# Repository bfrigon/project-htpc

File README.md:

HTPC
====

Project page at http://www.bfrigon.com/posts/projects/htpc/

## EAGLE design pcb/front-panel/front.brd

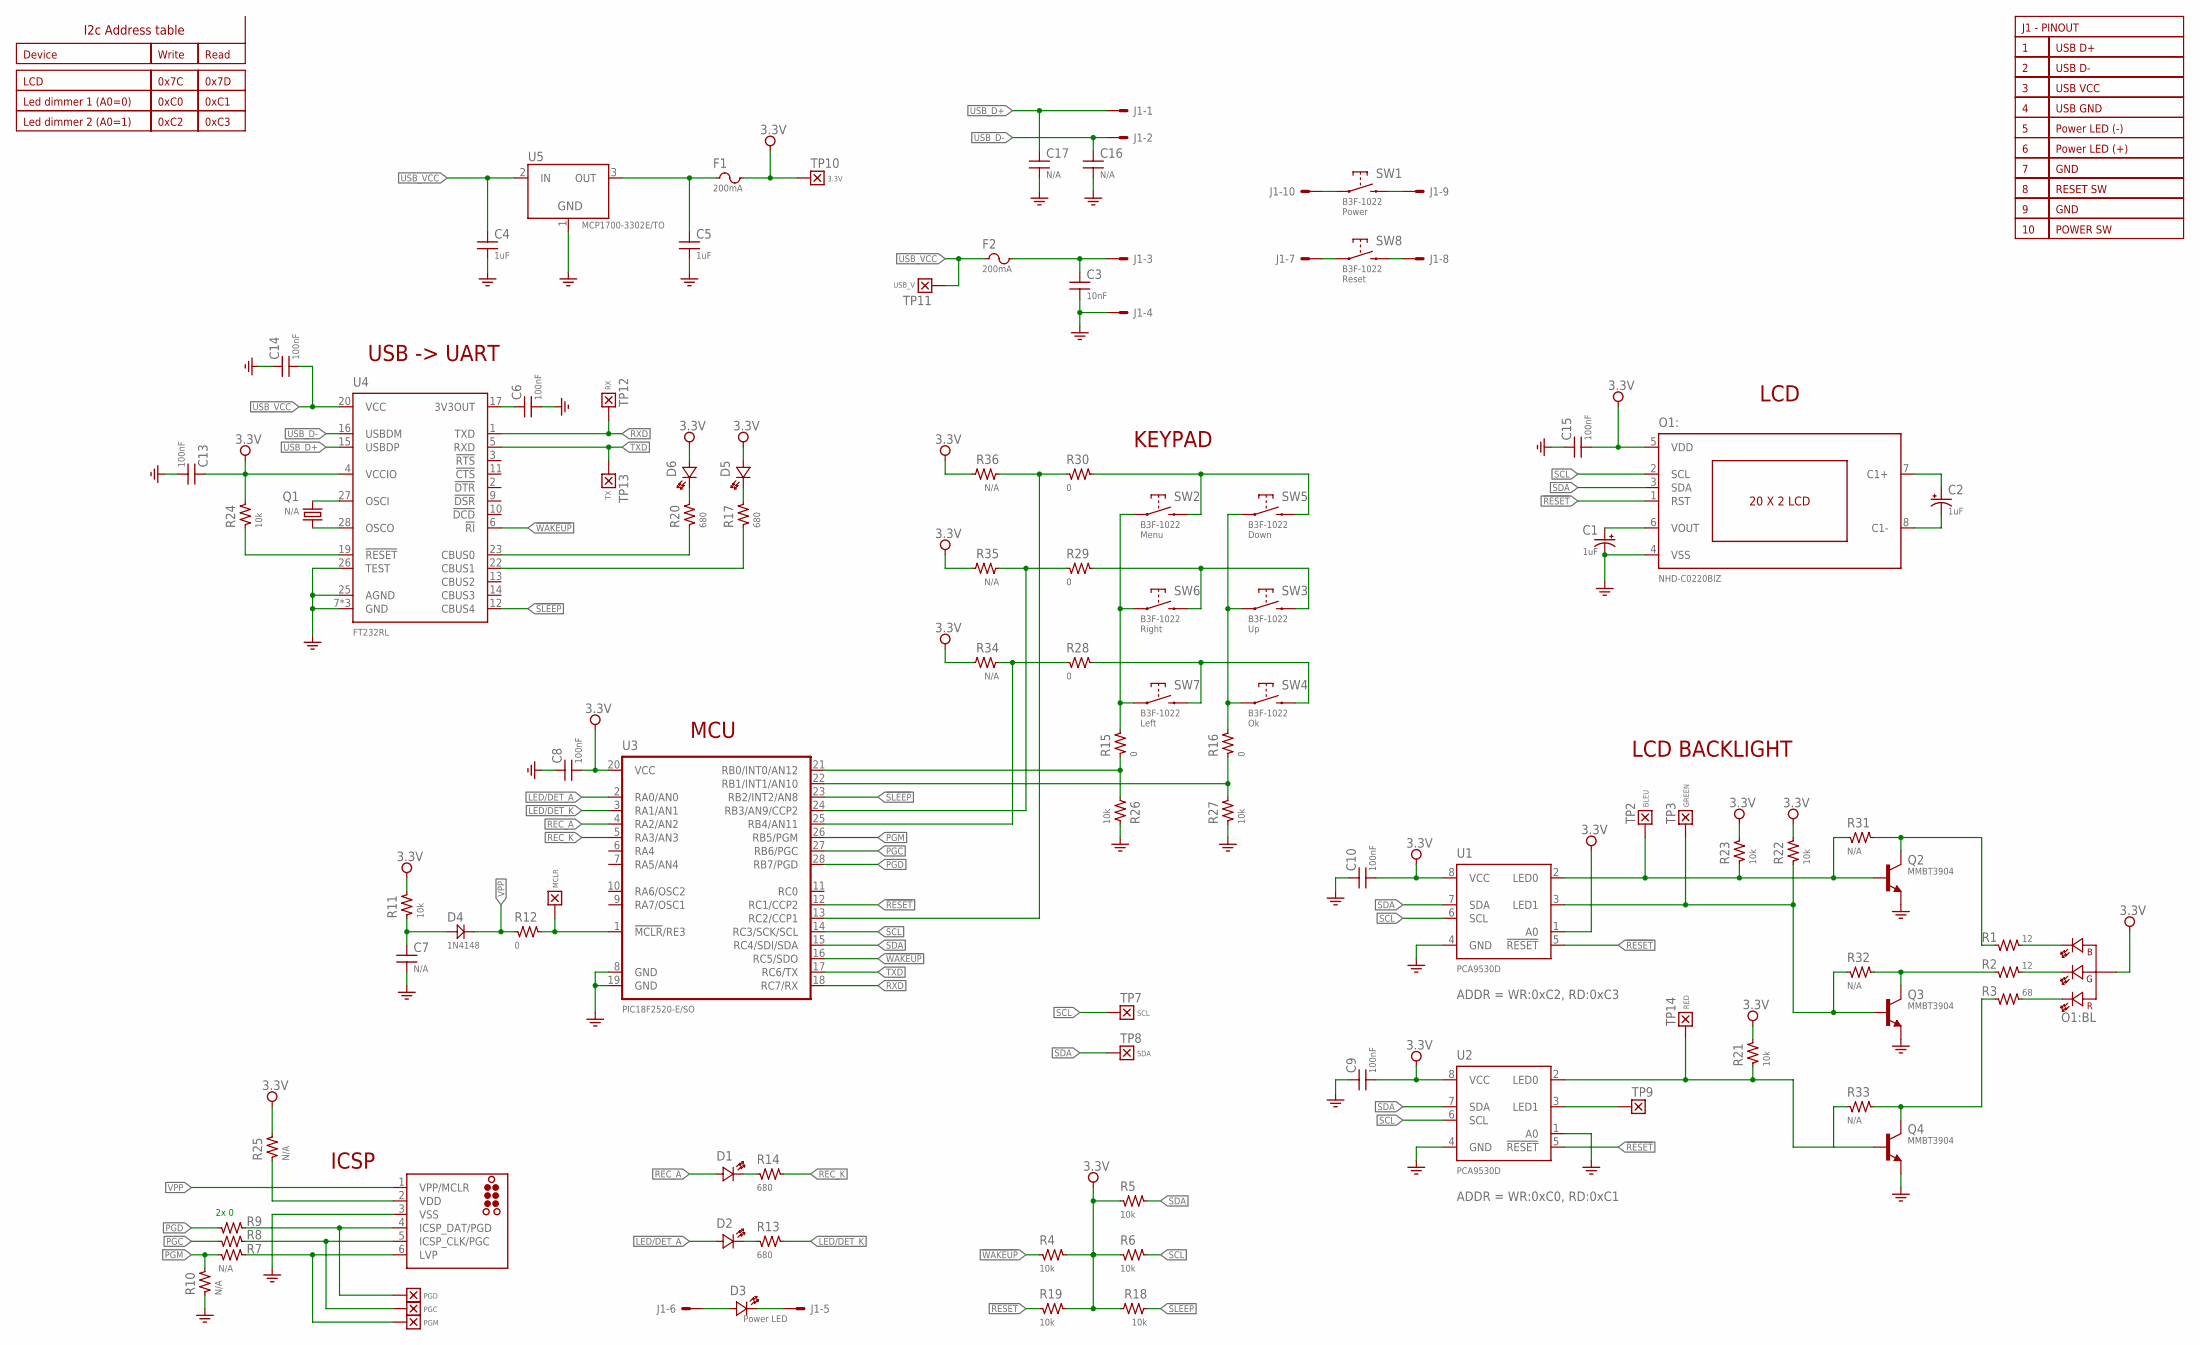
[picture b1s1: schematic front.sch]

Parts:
C1, C2: 1uF; CAP_S0805
C3: 10nF; SMD_0805
C4, C5: 1uF; SMD_0805
C6, C8, C9, C10, C13, C14, C15: 100nF; SMD_0603
C7, C16, C17: N/A; SMD_0603
D1, D2, D3: {ATTR:COLOR}; LED_2X5
D4: 1N4148; DIODE_0603
D5, D6: LED-0805; CHIPLED_0805
F1, F2: 200mA; SMD_1206
J1: DL-100-HEADER-10-V; 534206-5
J10: TC2030-MCP
O1: NHD-C0220BIZ; NHD-CO220BIZ
Q1: N/A; MM20SS
Q2, Q3, Q4: MMBT3904; SOT23
R1, R2: 12; SMD_1206
R3: 68; SMD_1206
R4, R5, R6, R18, R19, R21, R22, R23: 10k; SMD_0805
R7, R10, R25, R34, R35, R36: N/A; SMD_0603
R8, R9, R12, R28: 0; SMD_0603
R11, R24, R26, R27: 10k; SMD_0603
R13, R14, R17, R20: 680; SMD_0805
R15, R16, R29, R30: 0; SMD_0805
R31, R32, R33: N/A; SMD_1206
SW1, SW2, SW3, SW4, SW5, SW6, SW7, SW8: B3F-1022; B3F-10XX
TP1: MCLR; TP_050
TP2: BLEU; TP_050
TP3: GREEN; TP_050
TP4: PGD; TP_050
TP5: PGC; TP_050
TP6: PGM; TP_050
TP7: SCL; TP_050
TP8: SDA; TP_050
TP9: TEST_POINT-050; TP_050
TP10: 3.3V; TP_050
TP11: USB_V; TP_050
TP12: RX; TP_050
TP13: TX; TP_050
TP14: RED; TP_050
U1, U2: PCA9530D; SOIC8
U3: PIC18F2520-E/SO; SOIC28
U4: FT232RL; SSOP28
U5: MCP1700-3302E/TO; TO92

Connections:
3.3V: C8.2, C9.2, C10.2, C13.1, C15.2, D5.A, D6.A, F1.2, O1.5 (VDD), O1.A, R4.2, R5.1, R6.1, R11.2, R18.2, R19.2, R21.2, R22.2, R23.2, R24.2, R25.2, R34.2, R35.2, R36.2, TP10.1, U1.1 (A0), U1.8 (VCC), U2.8 (VCC), U3.20 (VCC), U4.4 (VCCIO)
!RESET: O1.1 (RST), R19.1, U1.5 (!RESET), U2.5 (!RESET), U3.12 (RC1/CCP2)
!SLEEP: R18.1, U3.23 (RB2/INT2/AN8), U4.12 (CBUS4)
!WAKEUP: R4.1, U3.16 (RC5/SDO), U4.6 (!RI)
GND: C1.-, C3.2, C4.2, C5.2, C6.2, C7.2, C8.1, C9.1, C10.1, C13.2, C14.1, C15.1, C16.2, C17.2, J1.4, J10.3 (VSS), O1.4 (VSS), Q2.2 (E), Q3.2 (E), Q4.2 (E), R10.1, R26.1, R27.1, U1.4 (GND), U2.1 (A0), U2.4 (GND), U3.8 (GND), U3.19 (GND), U4.7 (GND), U4.18 (GND), U4.21 (GND), U4.25 (AGND), U4.26 (TEST), U5.1 (GND)
LED/DET_A: D2.A, U3.2 (RA0/AN0)
LED/DET_K: R13.2, U3.3 (RA1/AN1)
unnamed: O1.BK, R1.2
unnamed: O1.GK, R2.2
unnamed: O1.RK, R3.2
unnamed: Q2.1 (B), R23.1, R31.1, TP2.1, U1.2 (LED0)
unnamed: Q3.1 (B), R22.1, R32.1, TP3.1, U1.3 (LED1)
unnamed: Q2.3 (C), R1.1, R31.2
unnamed: J1.10, SW1.3 (1), SW1.4 (1)
unnamed: J1.9, SW1.1 (2), SW1.2
unnamed: J1.8, SW8.1 (2), SW8.2
unnamed: J1.7, SW8.3 (1), SW8.4 (1)
unnamed: D3.A, J1.6
unnamed: D3.K, J1.5
unnamed: C6.1, U4.17 (3V3OUT)
unnamed: J10.6 (LVP), R7.2, TP6.1
unnamed: J10.5 (ICSP_CLK/PGC), R8.2, TP5.1
unnamed: J10.4 (ICSP_DAT/PGD), R9.2, TP4.1
unnamed: R15.1, R26.2, U3.21 (RB0/INT0/AN12)
unnamed: R16.1, R27.2, U3.22 (RB1/INT1/AN10)
unnamed: R30.1, R36.1, U3.13 (RC2/CCP1)
unnamed: R29.1, R35.1, U3.24 (RB3/AN9/CCP2)
unnamed: R28.1, R34.1, U3.25 (RB4/AN11)
unnamed: R12.2, TP1.1, U3.1 (!MCLR!/RE3)
unnamed: D2.K, R13.1
unnamed: R15.2, SW2.3 (1), SW2.4 (1), SW6.3 (1), SW6.4 (1), SW7.3 (1), SW7.4 (1)
unnamed: D1.K, R14.1
unnamed: R16.2, SW3.3 (1), SW3.4 (1), SW4.3 (1), SW4.4 (1), SW5.3 (1), SW5.4 (1)
unnamed: R17.1, U4.22 (CBUS1)
unnamed: R20.1, U4.23 (CBUS0)
unnamed: D6.K, R20.2
unnamed: D5.K, R17.2
unnamed: Q3.3 (C), R2.1, R32.2
unnamed: Q4.3 (C), R3.1, R33.2
unnamed: C5.1, F1.1, U5.3 (OUT)
unnamed: Q4.1 (B), R21.1, R33.1, TP14.1, U2.2 (LED0)
unnamed: C3.1, F2.2, J1.3
unnamed: Q1.1, U4.27 (OSCI)
unnamed: Q1.4 (2), U4.28 (OSCO)
unnamed: C2.+, O1.7 (C1+)
unnamed: C2.-, O1.8 (C1-)
unnamed: C1.+, O1.6 (VOUT)
unnamed: TP9.1, U2.3 (LED1)
unnamed: R24.1, U4.19 (!RESET)
unnamed: J10.2 (VDD), R25.1
unnamed: C7.1, D4.A, R11.1
unnamed: R30.2, SW2.1 (2), SW2.2, SW5.1 (2), SW5.2
unnamed: R29.2, SW3.1 (2), SW3.2, SW6.1 (2), SW6.2
unnamed: R28.2, SW4.1 (2), SW4.2, SW7.1 (2), SW7.2
PGC: R8.1, U3.27 (RB6/PGC)
PGD: R9.1, U3.28 (RB7/PGD)
PGM: R7.1, R10.2, U3.26 (RB5/PGM)
REC_A: D1.A, U3.4 (RA2/AN2)
REC_K: R14.2, U3.5 (RA3/AN3)
RXD: TP12.1, U3.18 (RC7/RX), U4.1 (TXD)
SCL: O1.2 (SCL), R6.2, TP7.1, U1.6 (SCL), U2.6 (SCL), U3.14 (RC3/SCK/SCL)
SDA: O1.3 (SDA), R5.2, TP8.1, U1.7 (SDA), U2.7 (SDA), U3.15 (RC4/SDI/SDA)
TXD: TP13.1, U3.17 (RC6/TX), U4.5 (RXD)
USB_D+: C17.1, J1.1, U4.15 (USBDP)
USB_D-: C16.1, J1.2, U4.16 (USBDM)
USB_VCC: C4.1, C14.2, F2.1, TP11.1, U4.20 (VCC), U5.2 (IN)
VPP: D4.K, J10.1 (VPP/MCLR), R12.1

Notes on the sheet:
I2c Address table
LCD BACKLIGHT
USB -> UART
ICSP
LCD
MCU
2x 0
KEYPAD

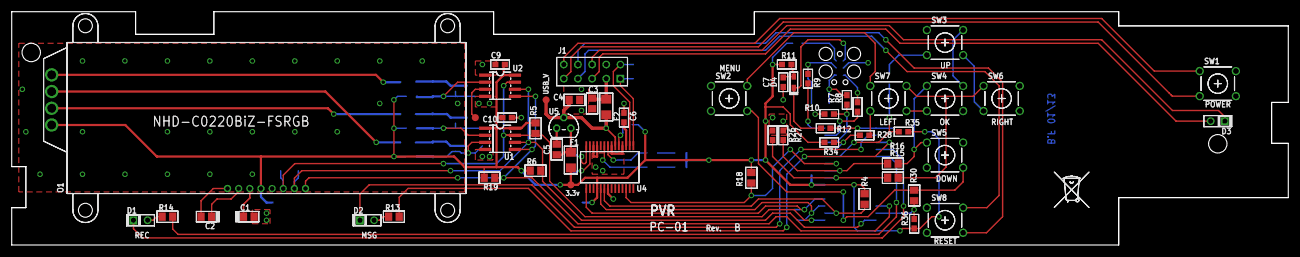
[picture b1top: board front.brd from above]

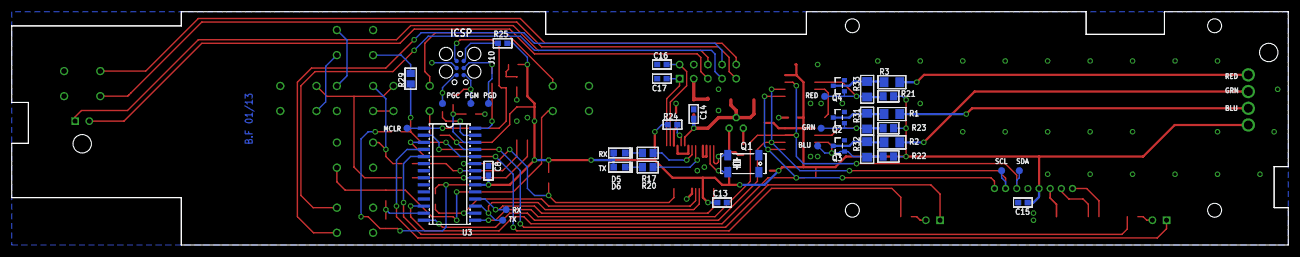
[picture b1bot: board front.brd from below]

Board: 2 copper layers, 229.1 x 41.9 mm, 97 parts (41 on the bottom side), 67 nets.

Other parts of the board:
U$1: INFO
U$2: TRASH_SMALL
U$3: INFO_AUTHOR
U$4: INFO_DATE

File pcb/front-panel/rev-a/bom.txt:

Qty. Part ID                                Description                                      Mfg. SKU              Manufacturer                Package      Value
1    X1                                     10 Pos - Dual Row - 2.54mm Receptacle - Vertical SIP110-PPPC-D05-ST-BK Sullins Connector Solutions 534206-5     -    
8    SW1, SW2, SW3, SW4, SW5, SW6, SW7, SW8 Tactile switch - 6x6mm - 5mm Pitch - 150g        B3F-1022              Omron Electronics           B3F-10XX     -    
1    O1                                     Alphanumeric LCD module 20x2 - RGB Backlight     NHD-C0220BIZ          Newheaven Display           NHD-CO220BIZ -    
2    U1, U2                                 8-bit I2C-bus LED dimmer                         PCA9530D              NXP Semiconductors          SOIC8        -    
1    U3                                     Microcontroller 32k PROG / 1536 RAM / 256 EEPROM PIC18F2520-E/SO       -                           SOIC28       -    
3    T1, T2, T3                             PNP Transistor                                   MMBT3906              -                           SOT23-BEC    -    
1    U4                                     USB to serial UART interface                     FT232RL               -                           SSOP28       -    
1    U5                                     Low-dropout (LDO) Voltage Regulator - 3.3v       MCP1700-3302E/TO      Microchip                   TO92         -    
4    R7, R8, R9, R12                        Resistor - SMT 0603 - 0                          -                     -                           SMT 0603     0    
3    L1, R15, R16                           Resistor - SMT 0805 - 0                          -                     -                           SMT 0805     0    
2    C1, C2                                 Electrolytic capacitor - SMT 0805 - 1uF          -                     -                           CAP_S0805    1uF  
2    C4, C5                                 Capacitor - SMT 0805 - 1uF                       -                     -                           SMT 0805     1uF  
2    R1, R2                                 Resistor - SMT 1206 - 6.8                        -                     -                           SMT 1206     6.8  
3    R10, R11, R17                          Resistor - SMT 0603 - 10k                        -                     -                           SMT 0603     10k  
5    R4, R5, R6, R18, R19                   Resistor - SMT 0805 - 10k                        -                     -                           SMT 0805     10k  
1    C3                                     Capacitor - SMT 0805 - 10nF                      -                     -                           SMT 0805     10nF 
1    R3                                     Resistor - SMT 1206 - 33                         -                     -                           SMT 1206     33   
2    C16, C17                               Capacitor - SMT 0603 - 47nF                      -                     -                           SMT 0603     47nF 
7    C6, C8, C9, C10, C13, C14, C15         Capacitor - SMT 0603 - 100nF                     -                     -                           SMT 0603     100nF
2    F1, F2                                 Fuse - SMT 1206 - 250mA                          -                     -                           SMD_1206     250mA
3    R13, R14, R20                          Resistor - SMT 0805 - 680                        -                     -                           SMT 0805     680  
2    D2, D3                                 Led 2x5mm - Green                                -                     -                           2x5mm        Green
1    D6                                     Led Chip 0805 - Green                            -                     -                           SMT 0805     Green
1    D1                                     Led 2x5mm - Red                                  -                     -                           2x5mm        Red

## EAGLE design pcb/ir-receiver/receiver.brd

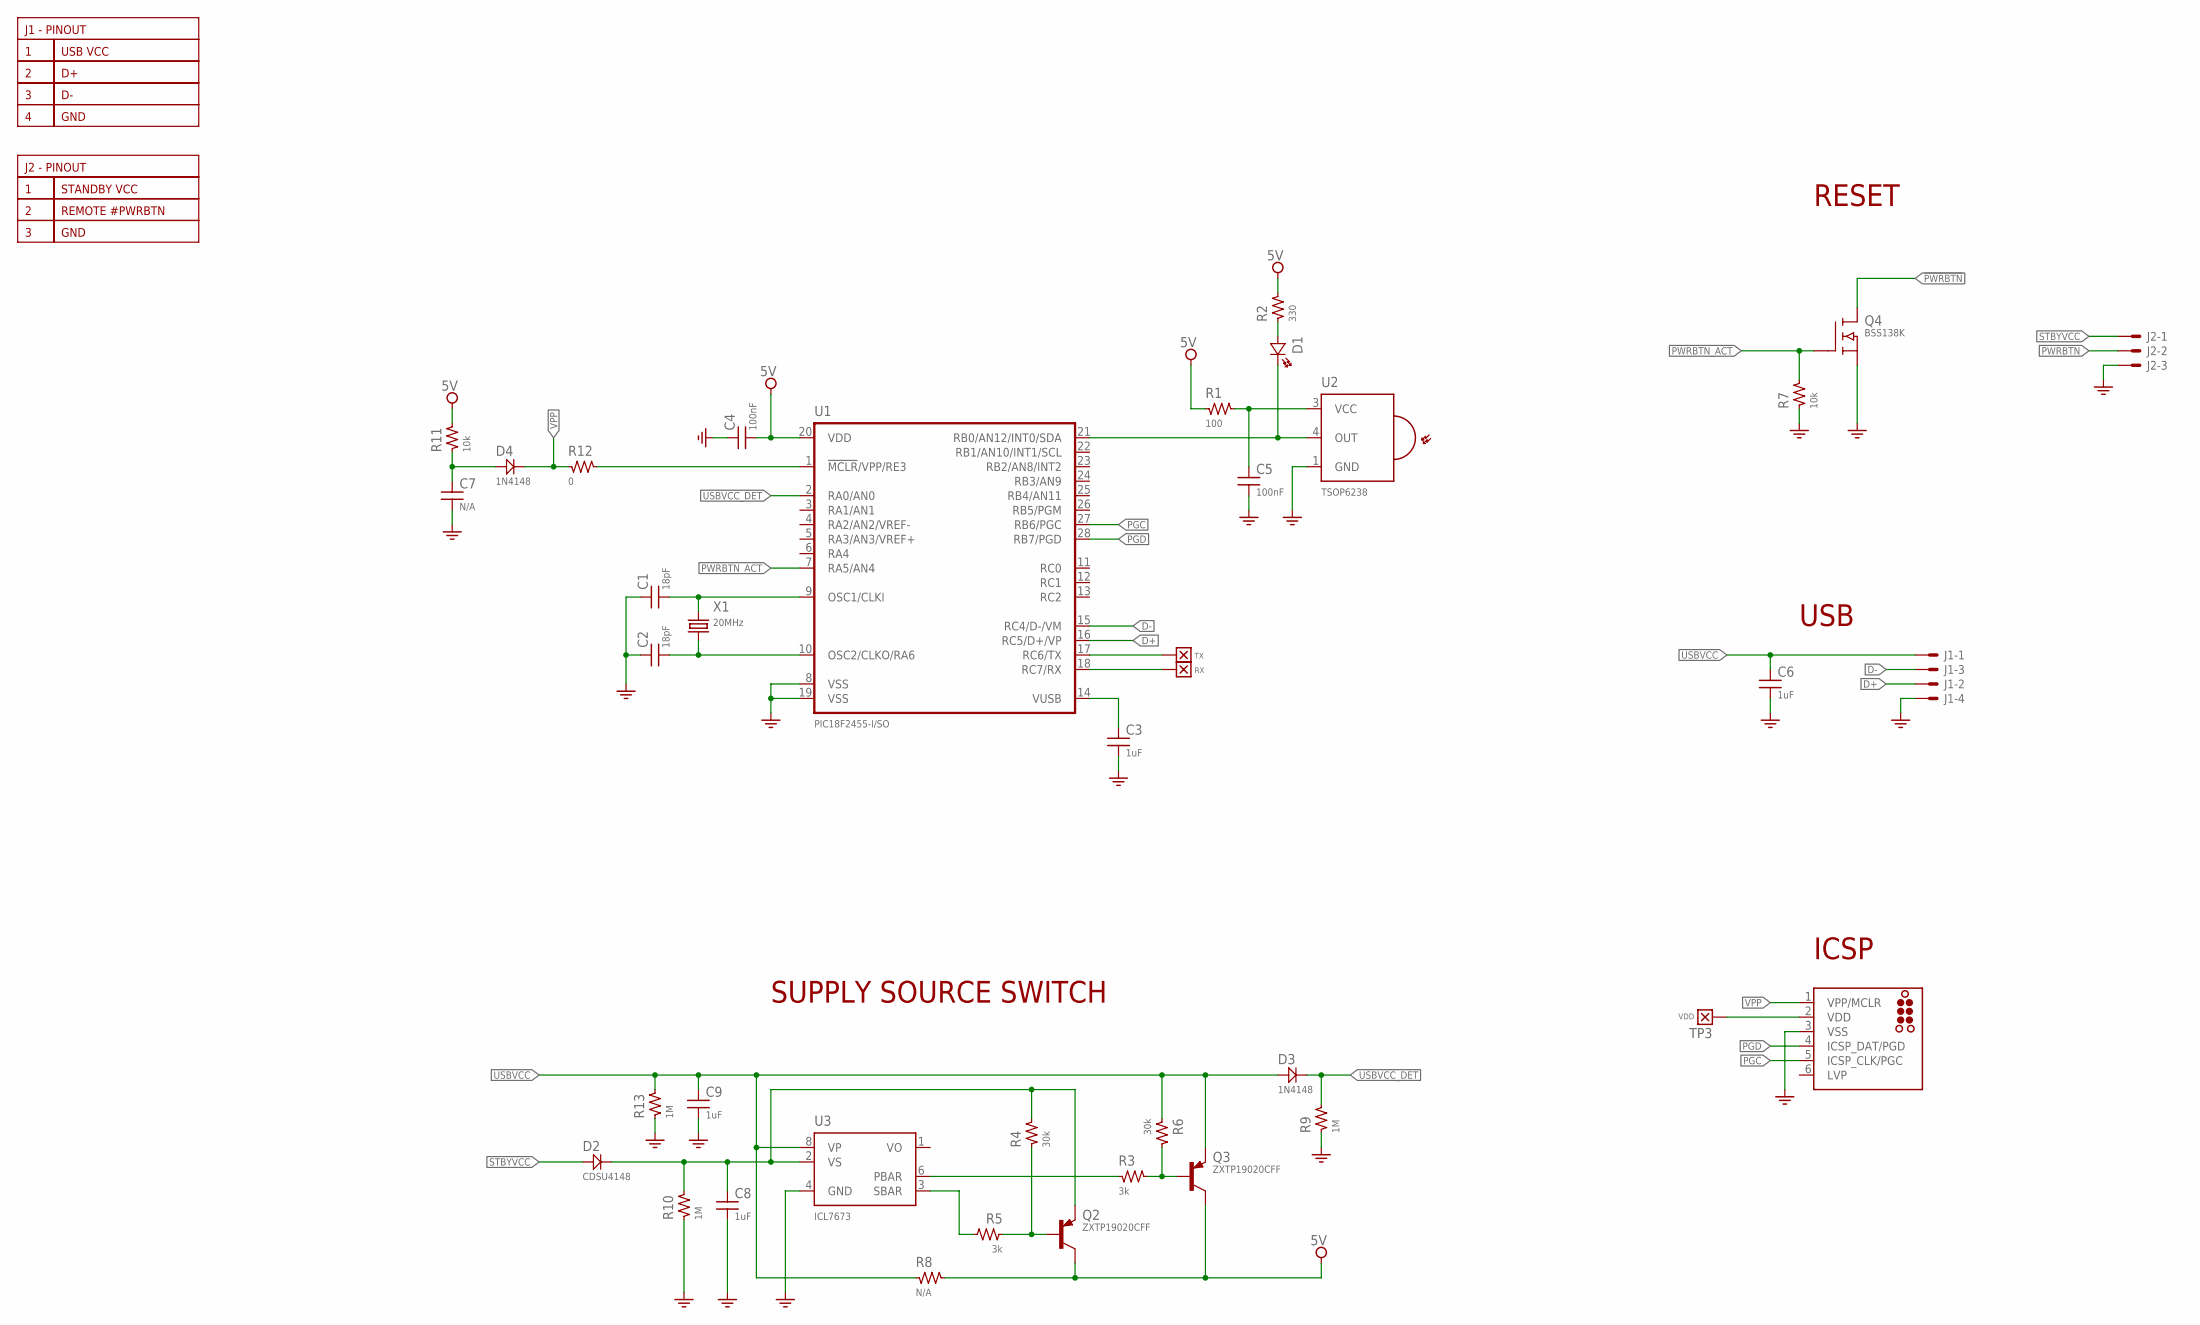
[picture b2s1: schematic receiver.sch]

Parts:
C1, C2: 18pF; SMD_0603
C3, C6, C8, C9: 1uF; SMD_0603
C4, C5: 100nF; SMD_0603
C7: N/A; SMD_0603
D1: {ATTR:COLOR}; CHIPLED_0805
D2: CDSU4148; DIODE_0603
D3, D4: 1N4148; DIODE_0603
J1: SNG-100-HEADER-04-FL-RA; 22-05-3041
J2: SNG-100-HEADER-03-FL-RA; 22-05-3031
J10: TC2030-MCP
Q2, Q3: ZXTP19020CFF; SOT23
Q4: BSS138K; SOT23
R1: 100; SMD_0603
R2: 330; SMD_0603
R3, R5: 3k; SMD_0603
R4, R6: 30k; SMD_0603
R7, R11: 10k; SMD_0603
R8: N/A; SMD_0805
R9, R10, R13: 1M; SMD_0603
R12: 0; SMD_0603
TP1: TX; TP_050
TP2: RX; TP_050
TP3: VDD; TP_050
U1: PIC18F2455-I/SO; SOIC28
U2: TSOP6238; TSOP62XX
U3: ICL7673; SOIC8
X1: 20MHz; SM49

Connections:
5V: C4.2, Q2.3 (C), Q3.3 (C), R1.1, R2.2, R8.2, R11.2, U1.20 (VDD)
!PWRBTN: J2.2, Q4.3 (D)
D+: J1.2, U1.16 (RC5/D+/VP)
D-: J1.3, U1.15 (RC4/D-/VM)
GND: C1.1, C2.1, C3.2, C4.1, C5.2, C6.2, C7.2, C8.2, C9.2, J1.4, J2.3, J10.3 (VSS), Q4.2 (S), R7.1, R9.1, R10.1, R13.1, U1.8 (VSS), U1.19 (VSS), U2.1 (GND), U3.4 (GND)
IR: D1.K, U1.21 (RB0/AN12/INT0/SDA), U2.4 (OUT)
unnamed: Q2.1 (B), R4.1, R5.1
unnamed: D1.A, R2.1
unnamed: C5.1, R1.2, U2.3 (VCC)
unnamed: Q3.1 (B), R3.2, R6.2
unnamed: R3.1, U3.6 (PBAR)
unnamed: R5.2, U3.3 (SBAR)
unnamed: C8.1, D2.K, Q2.2 (E), R4.2, R10.2, U3.2 (VS)
unnamed: J10.2 (VDD), TP3.1
unnamed: R12.2, U1.1 (!MCLR!/VPP/RE3)
unnamed: C7.1, D4.A, R11.1
OSC1: C1.2, U1.9 (OSC1/CLKI), X1.1
OSC2: C2.2, U1.10 (OSC2/CLKO/RA6), X1.2
PGC: J10.5 (ICSP_CLK/PGC), U1.27 (RB6/PGC)
PGD: J10.4 (ICSP_DAT/PGD), U1.28 (RB7/PGD)
PWRBTN_ACT: Q4.1 (G), R7.2, U1.7 (RA5/AN4)
RX: TP2.1, U1.18 (RC7/RX)
STBYVCC: D2.A, J2.1
TX: TP1.1, U1.17 (RC6/TX)
USBVCC: C6.1, C9.1, D3.A, J1.1, Q3.2 (E), R6.1, R8.1, R13.2, U3.8 (VP)
USBVCC_DET: D3.K, R9.2, U1.2 (RA0/AN0)
VO: U3.1 (VO)
VPP: D4.K, J10.1 (VPP/MCLR), R12.1
VUSB: C3.1, U1.14 (VUSB)

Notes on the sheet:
SUPPLY SOURCE SWITCH
ICSP
USB
RESET

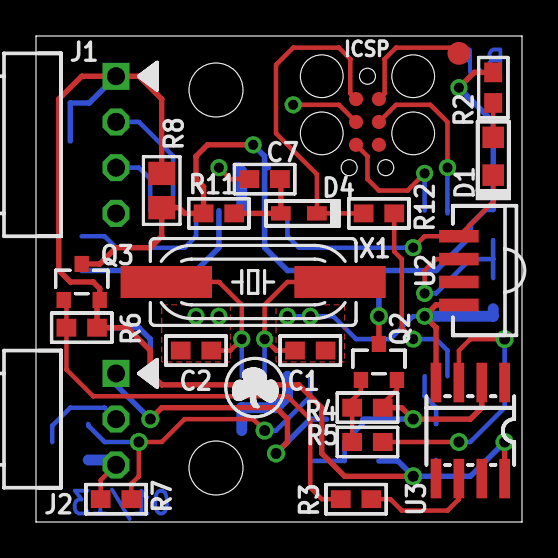
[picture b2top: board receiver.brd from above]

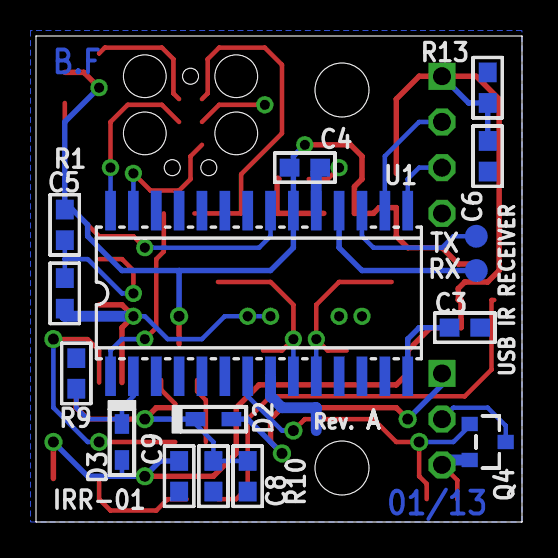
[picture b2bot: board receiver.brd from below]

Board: 2 copper layers, 27.0 x 27.0 mm, 44 parts (18 on the bottom side), 28 nets.

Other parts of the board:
U$1: INFO_DATE
U$2, U$3: ARROW
U$4: LOGO2
U$5: INFO_AUTHOR

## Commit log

2014-09-17 Fixed indentations
2015-01-31 Added host suspend/resume handling
2015-01-31 Changed bootscreen to KODI
2015-01-31 Changed BIOS boot logo to KODI

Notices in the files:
parts and their libraries:
Connectors: ©2009 ROFA.cz
